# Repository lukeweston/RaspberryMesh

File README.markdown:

**Raspberry Pi sensor / power supply / LCD / 802.15.4 mesh network expansion board**   
Luke Weston, 2012     

Released as Open Hardware under the CERN Open Hardware License - http://ohwr.org/cernohl  

This Raspberry Pi add-on daughterboard or shield incorporates a 16x2 alphanumeric LCD display (standard HD44780-type display), a visible light sensor, a barometric pressure
and temperature sensor, a smal RGB LED for visual output, and an Atmel ATmega128RFA1 AVR microcontroller with integrated IEEE 802.15.4 mesh network transceiver with support
for IPv6/6LoWPAN. 

A real-time clock with battery backup and a buck-converter voltage regulator allowing a wide input voltage range between 7 and 35 volts to power the Raspberry Pi are also
included. Voltages up to 35V can simply be plugged into the 2.1mm power jack to power the entire system flexibly.

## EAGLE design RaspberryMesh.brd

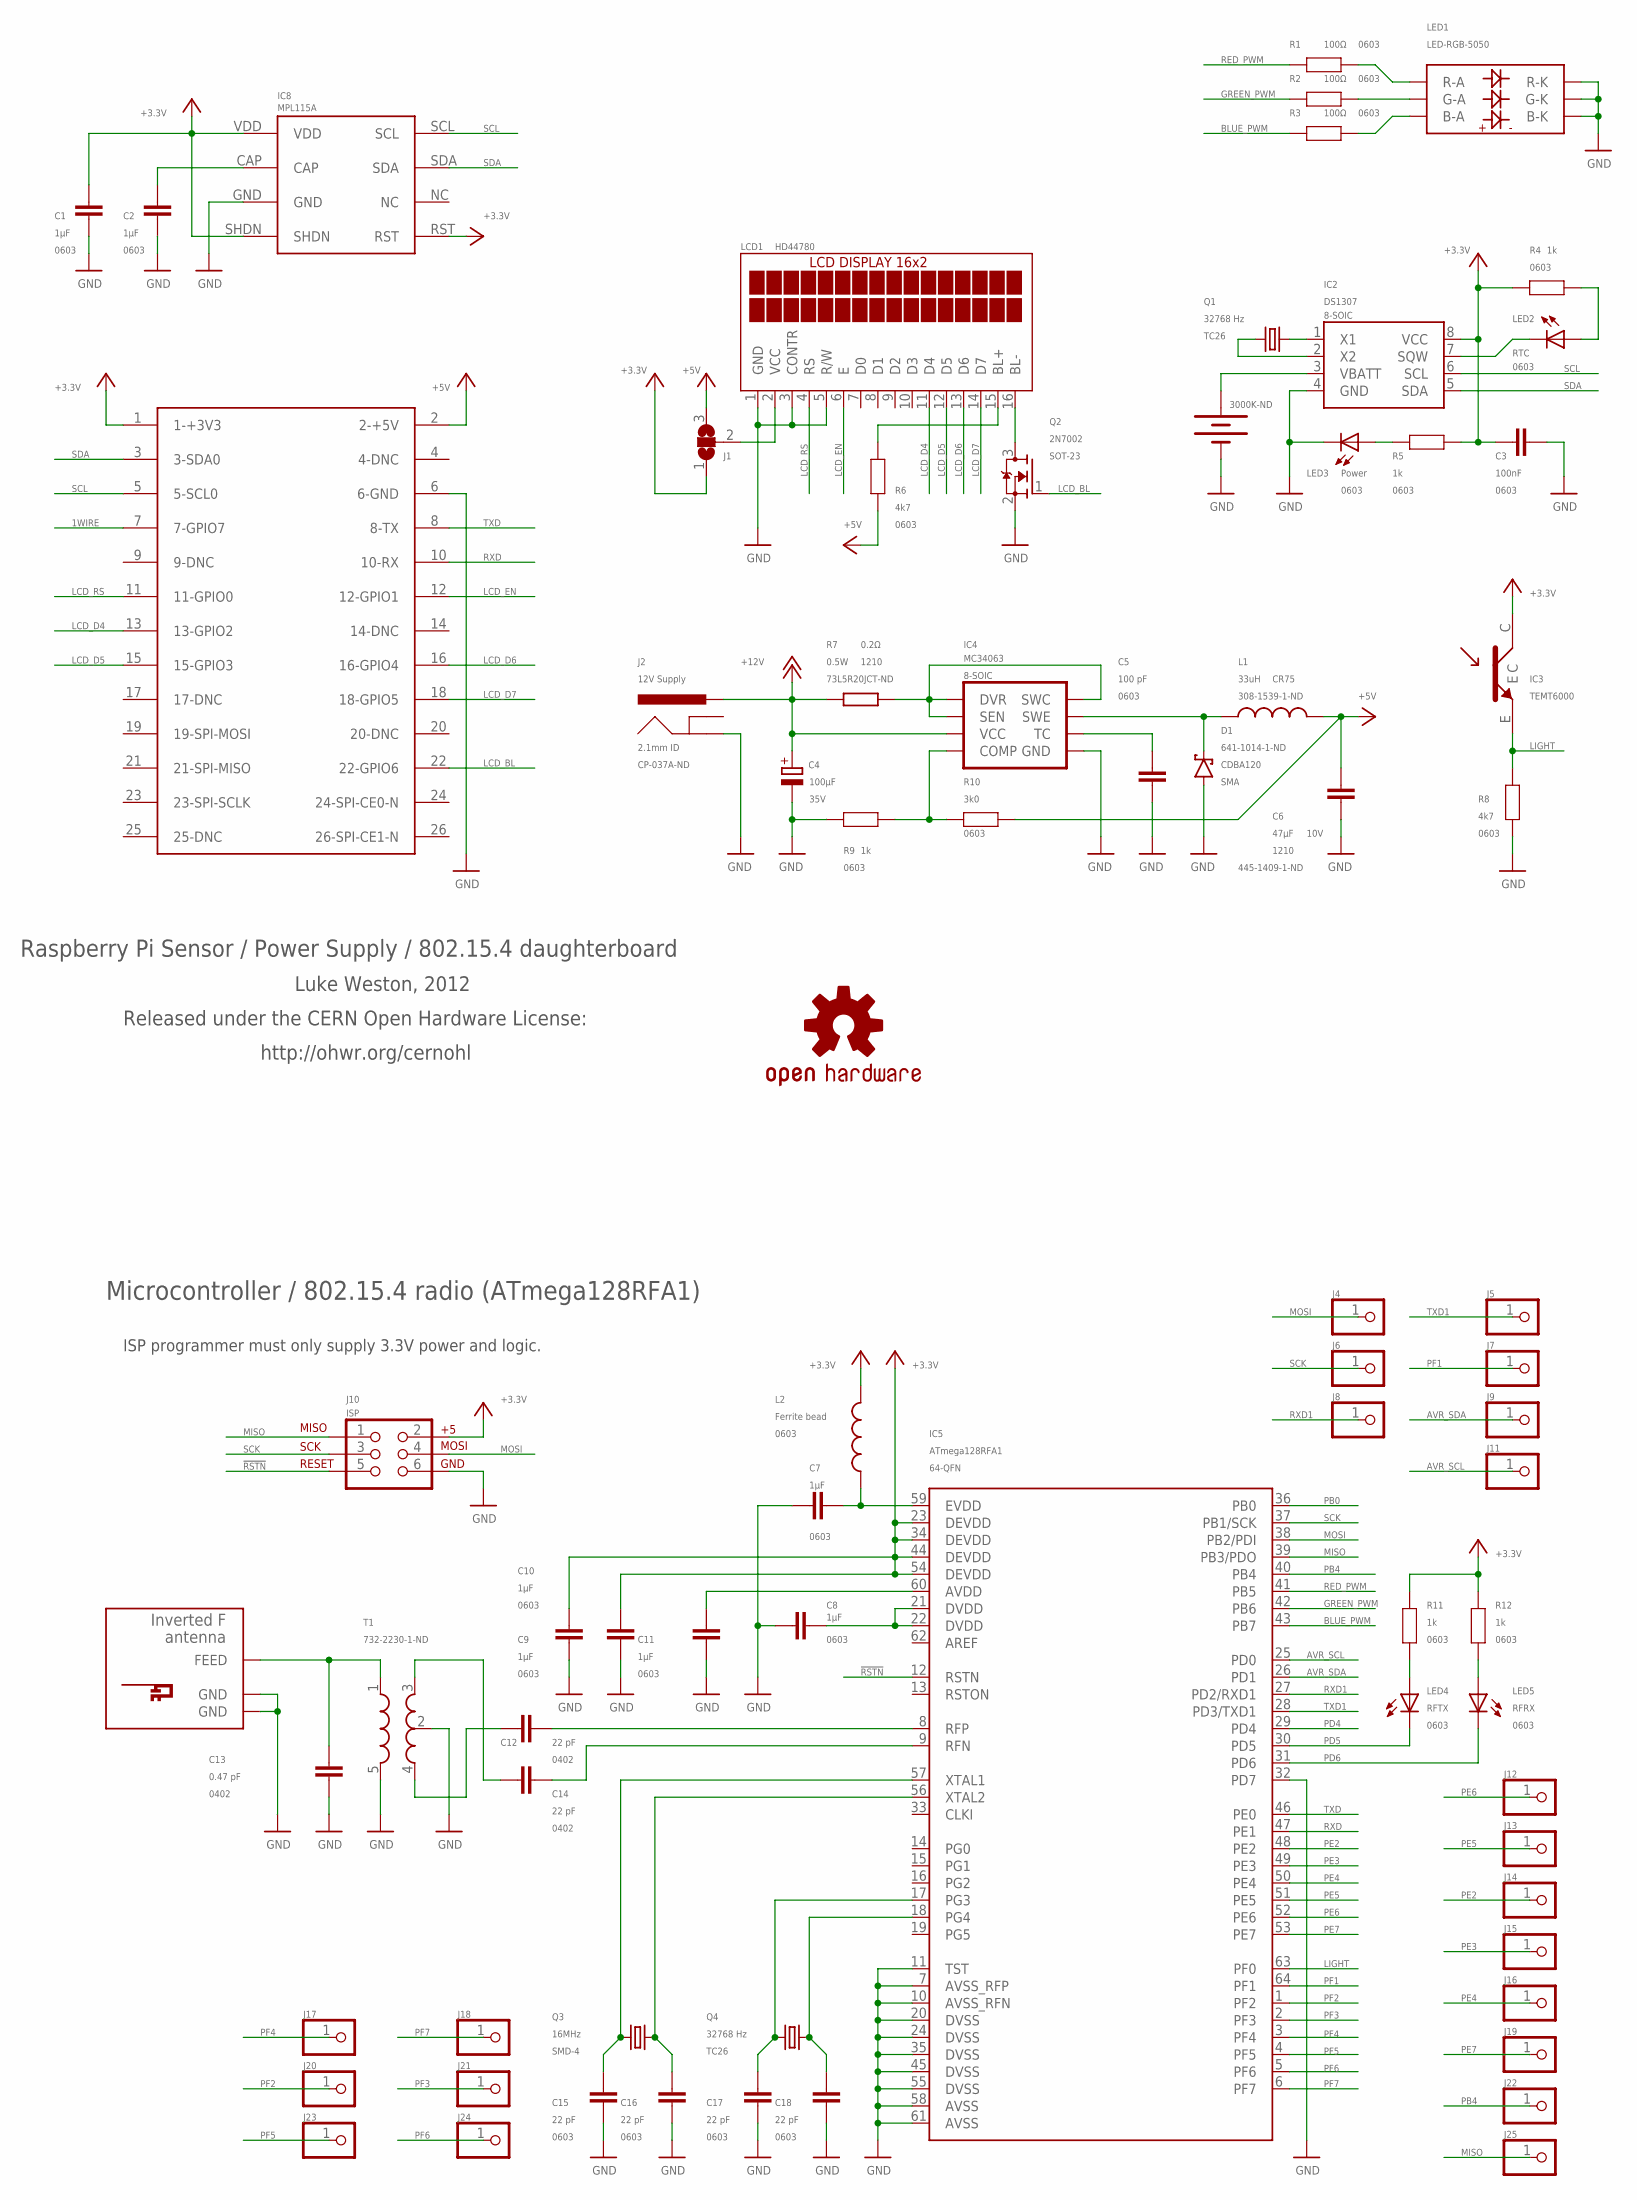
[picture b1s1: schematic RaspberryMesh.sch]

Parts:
A1: INVERTED_F_ANTENNA+2; DN007+2
B1: 3000K-ND; BATTCON_12MM
C1, C2, C7, C8, C9, C10, C11: 1µF; 0603
C3: 100nF; 0603
C4: 100µF; E2,5-6; VOLTAGE 35V
C5: 100 pF; 0603
C6: 47µF; C1210; VOLTAGE 10V
C12, C14: 22 pF; C0402
C13: 0.47 pF; C0402
C15, C16, C17, C18: 22 pF; 0603
D1: CDBA120; SMA
IC1: MPL115A
IC2: DS1307; SO08
IC3: TEMT6000
IC4: MC34063; SO08@1
IC5: ATmega128RFA1; QFN-64
J1: SJ2W; SJ_2
J2: 12V Supply; POWER_JACK_SLOT
J3: RASPBERRY-PI
J4, J5, J6, J7, J8, J9, J11, J12, J13, J14, J15, J16, J17, J18, J19, J20, J21, J22, J23, J24, J25: PINHD-1X1; 1X01
J10: ISP; 2X3-NS
L1: 33uH; CR75
L2: Ferrite bead; 0603
LCD1: HD44780; LCD_16X2_REAR
LED1: LED-RGB-5050
LED2: RTC; LED-0603
LED3: Power; LED-0603
LED4: RFTX; LED-0603
LED5: RFRX; LED-0603
Q1, Q4: 32768 Hz; CRYSTAL-32KHZ-SMD
Q2: 2N7002; SOT23
Q3: 16MHz; CRYSTAL-SMD-5X3
R1, R2, R3: 100Ω; 0603
R4, R5, R9, R11, R12: 1k; 0603
R6, R8: 4k7; 0603
R7: 0.2Ω; R1210
R10: 3k0; 0603
SY1: OSHW-LOGOS; OSHW-LOGO-S
T1: 732-2230-1-ND; BALUN

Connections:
1WIRE: J3.7 (7-GPIO7)
!RSTN: IC5.12 (RSTN), J10.5
+3V3: C1.2, C3.1, C9.1, C10.1, IC1.RST, IC1.SHDN, IC1.VDD, IC2.8 (VCC), IC3.C, IC5.23 (DEVDD), IC5.34 (DEVDD), IC5.44 (DEVDD), IC5.54 (DEVDD), J1.1, J3.1 (1-+3V3), J10.2, L2.2, R4.2, R5.2, R11.2, R12.2
+5V: C6.1, J1.3, J3.2 (2-+5V), L1.P$2 (2), R6.2, R10.1
+12V: C4.+, IC4.6 (VCC), J2.PWR, R7.1
AVR_SCL: IC5.25 (PD0), J11.1
AVR_SDA: IC5.26 (PD1), J9.1
BLUE_PWM: IC5.43 (PB7), R3.2
GND: A1.GND, A1.GND@1 (GND), B1.GND (-), C1.1, C2.1, C3.2, C4.-, C5.2, C6.2, C7.2, C8.2, C9.2, C10.2, C11.2, C13.2, C15.1, C16.1, C17.1, C18.1, D1.A, IC1.GND, IC2.4 (GND), IC4.4 (GND), IC5.7 (AVSS_RFP), IC5.10 (AVSS_RFN), IC5.11 (TST), IC5.20 (DVSS), IC5.24 (DVSS), IC5.32 (PD7), IC5.35 (DVSS), IC5.45 (DVSS), IC5.55 (DVSS), IC5.58 (AVSS), IC5.61 (AVSS), J2.GND, J3.6 (6-GND), J10.6, LCD1.1 (GND), LCD1.3 (CONTR), LCD1.5 (R/W), LED1.BK (B-K), LED1.GK (G-K), LED1.RK (R-K), LED3.C, Q2.2 (S), R8.1, R9.2, T1.2 (GND), T1.5 (GND)
GREEN_PWM: IC5.42 (PB6), R2.2
LCD_BL: J3.22 (22-GPIO6), Q2.1 (G)
LCD_D4: J3.13 (13-GPIO2), LCD1.11 (D4)
LCD_D5: J3.15 (15-GPIO3), LCD1.12 (D5)
LCD_D6: J3.16 (16-GPIO4), LCD1.13 (D6)
LCD_D7: J3.18 (18-GPIO5), LCD1.14 (D7)
LCD_EN: J3.12 (12-GPIO1), LCD1.6 (E)
LCD_RS: J3.11 (11-GPIO0), LCD1.4 (RS)
LIGHT: IC3.E, IC5.63 (PF0), R8.2
MISO: IC5.39 (PB3/PDO), J10.1, J25.1
MOSI: IC5.38 (PB2/PDI), J4.1, J10.4
unnamed: J1.2, LCD1.2 (VCC)
unnamed: IC4.1 (SWC), IC4.7 (SEN), IC4.8 (DVR), R7.2
unnamed: LCD1.15 (BL+), R6.1
unnamed: IC2.7 (SQW), LED2.C
unnamed: C5.1, IC4.3 (TC)
unnamed: LCD1.16 (BL-), Q2.3 (D)
unnamed: IC4.5 (COMP), R9.1, R10.2
unnamed: LED3.A, R5.1
unnamed: C2.2, IC1.CAP
unnamed: IC2.2 (X2), Q1.X1 (1)
unnamed: IC2.1 (X1), Q1.X2 (2)
unnamed: LED2.A, R4.1
unnamed: B1.PWR@1 (+), IC2.3 (VBATT)
unnamed: C14.2, T1.3 (OUT1)
unnamed: C12.2, T1.4 (OUT2)
unnamed: C16.2, IC5.56 (XTAL2), Q3.3 (2)
unnamed: C15.2, IC5.57 (XTAL1), Q3.1
unnamed: C17.2, IC5.17 (PG3), Q4.X1 (1)
unnamed: C18.2, IC5.18 (PG4), Q4.X2 (2)
unnamed: C8.1, IC5.21 (DVDD), IC5.22 (DVDD)
unnamed: C11.1, IC5.60 (AVDD)
unnamed: A1.FEED, C13.1, T1.1 (IN)
unnamed: C7.1, IC5.59 (EVDD), L2.1
unnamed: C12.1, IC5.8 (RFP)
unnamed: C14.1, IC5.9 (RFN)
unnamed: LED4.A, R11.1
unnamed: LED5.A, R12.1
unnamed: D1.K, IC4.2 (SWE), L1.P$1 (1)
unnamed: LED1.RA (R-A), R1.1
unnamed: LED1.GA (G-A), R2.1
unnamed: LED1.BA (B-A), R3.1
PB0: IC5.36 (PB0)
PB4: IC5.40 (PB4), J22.1
PD4: IC5.29 (PD4)
PD5: IC5.30 (PD5), LED4.C
PD6: IC5.31 (PD6), LED5.C
PE2: IC5.48 (PE2), J14.1
PE3: IC5.49 (PE3), J15.1
PE4: IC5.50 (PE4), J16.1
PE5: IC5.51 (PE5), J13.1
PE6: IC5.52 (PE6), J12.1
PE7: IC5.53 (PE7), J19.1
PF1: IC5.64 (PF1), J7.1
PF2: IC5.1 (PF2), J20.1
PF3: IC5.2 (PF3), J21.1
PF4: IC5.3 (PF4), J17.1
PF5: IC5.4 (PF5), J23.1
PF6: IC5.5 (PF6), J24.1
PF7: IC5.6 (PF7), J18.1
RED_PWM: IC5.41 (PB5), R1.2
RXD: IC5.47 (PE1), J3.10 (10-RX)
RXD1: IC5.27 (PD2/RXD1), J8.1
SCK: IC5.37 (PB1/SCK), J6.1, J10.3
SCL: IC1.SCL, IC2.6 (SCL), J3.5 (5-SCL0)
SDA: IC1.SDA, IC2.5 (SDA), J3.3 (3-SDA0)
TXD: IC5.46 (PE0), J3.8 (8-TX)
TXD1: IC5.28 (PD3/TXD1), J5.1

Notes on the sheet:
Raspberry Pi Sensor / Power Supply / 802.15.4 daughterboard
Luke Weston, 2012
Released under the CERN Open Hardware License:
http://ohwr.org/cernohl
ISP programmer must only supply 3.3V power and logic.
Microcontroller / 802.15.4 radio (ATmega128RFA1)

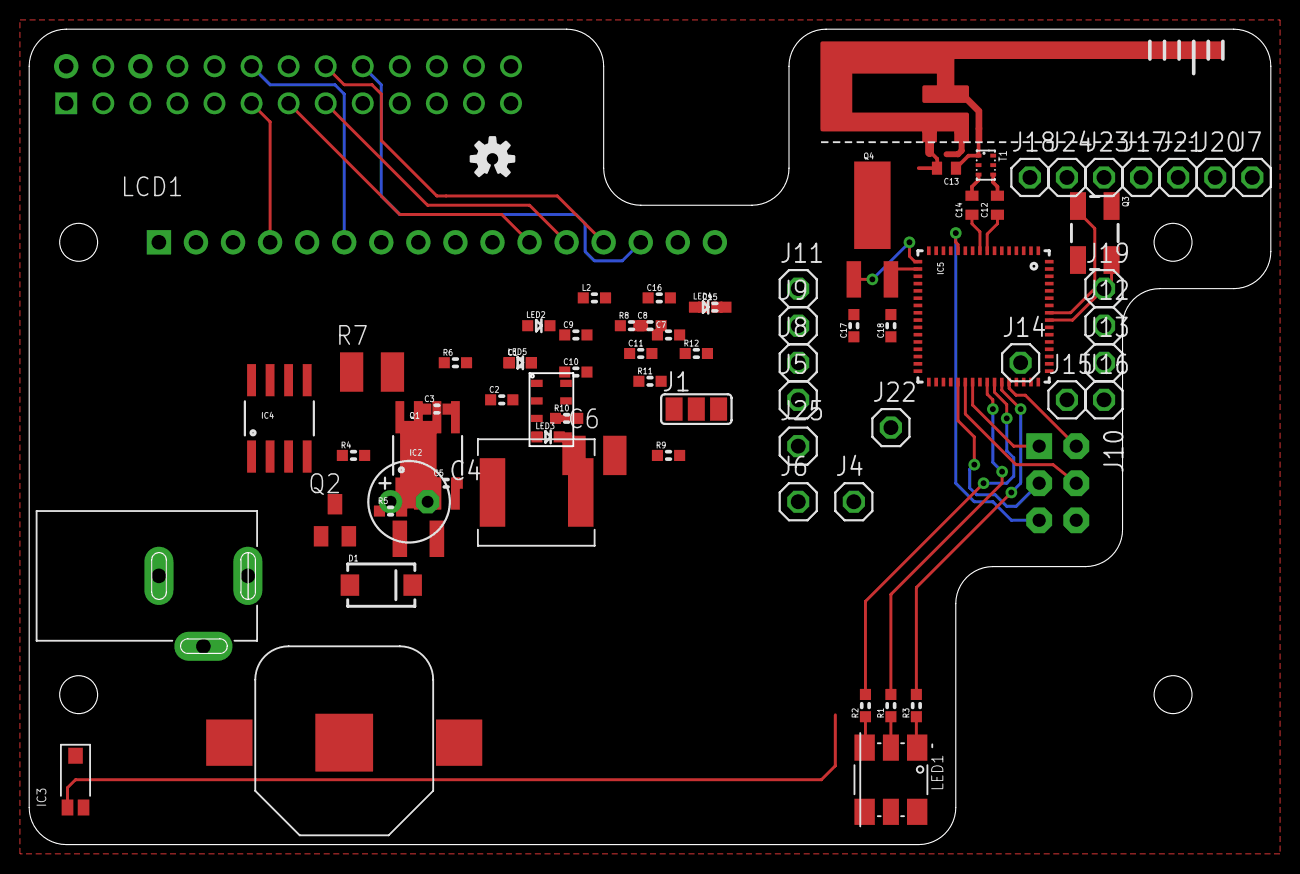
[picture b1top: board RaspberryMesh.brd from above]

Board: 2 copper layers, 85.0 x 55.8 mm, 77 parts (0 on the bottom side), 74 nets.
